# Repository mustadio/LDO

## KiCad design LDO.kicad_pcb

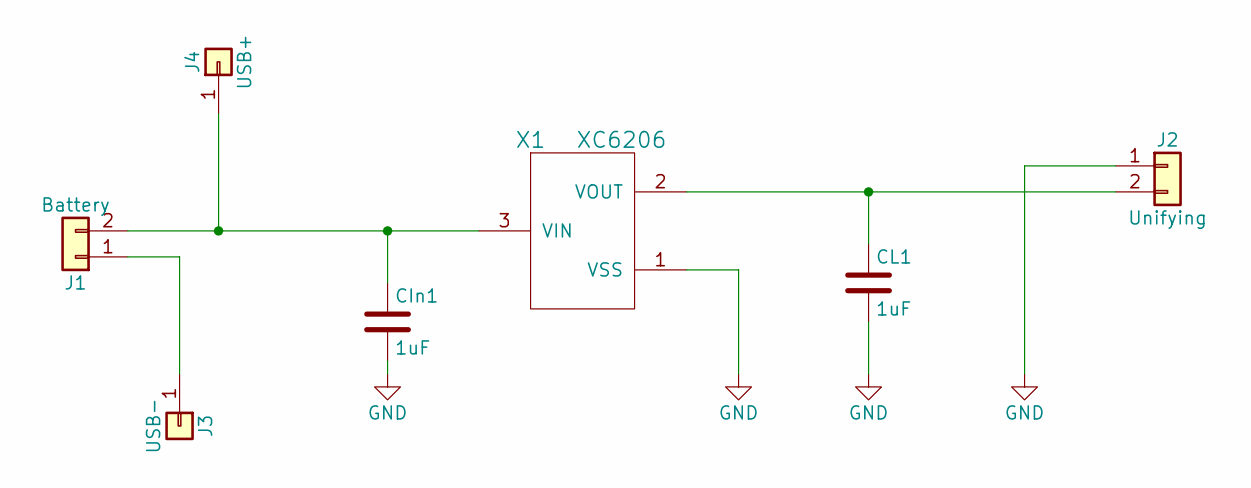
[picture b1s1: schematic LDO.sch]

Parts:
CIn1: 1uF; C_0805_HandSoldering
CL1: 1uF; C_0805_HandSoldering
J1: Battery; Socket_Strip_Angled_1x02_Pitch2.54mm
J2: Unifying; Socket_Strip_Angled_1x02_Pitch2.54mm
J3: USB-; Pin_Header_Straight_1x01_Pitch2.54mm
J4: USB+; Pin_Header_Straight_1x01_Pitch2.54mm
X1: XC6206; SOT-23

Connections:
GND: CIn1.2, CL1.2, J2.1, X1.1 (VSS)
unnamed: CIn1.1, J1.2, J4.1, X1.3 (VIN)
unnamed: CL1.1, J2.2, X1.2 (VOUT)
unnamed: J1.1, J3.1

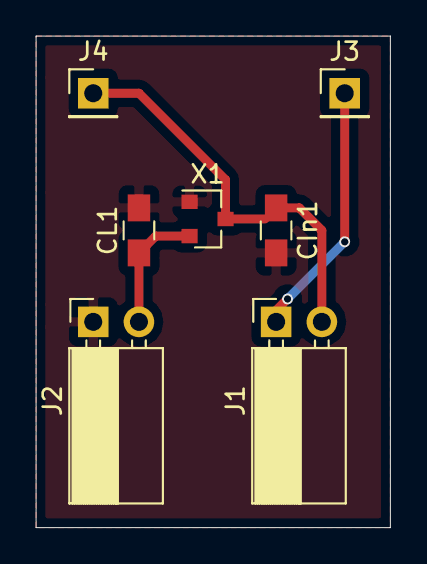
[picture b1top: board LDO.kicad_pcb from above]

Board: 2 copper layers, 19.7 x 27.3 mm, 7 parts (0 on the bottom side), 4 nets.
